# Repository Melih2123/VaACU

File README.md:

# VaACU
**Voltage and Amperage Control Unit**

VaACU is an open-source power management and battery charging platform designed to integrate multiple power sources into a single, organized system.

It supports **9–36 V DC input** and **220 V AC mains input**, converting incoming power into regulated **3.3 V, 5 V, and 12 V DC rails** while supporting battery charging, power-path management, current monitoring, and protection circuitry.

### Key Features
- Multiple power input options
- Regulated 3.3 V, 5 V, and 12 V power rails
- Integrated battery charging and backup power management
- Diode OR-ing for power-source isolation
- Current sensing using the INA293B2
- Fuse-based overcurrent protection
- Battery undervoltage protection
- ESP32-S3-based monitoring and control
- Open-source hardware design developed with KiCad

VaACU aims to provide a modular foundation for embedded systems that need flexible power input, battery backup, and centralized power management.

**Status:** Hardware design and validation hasnt been done, you the user might have to verify before usage.

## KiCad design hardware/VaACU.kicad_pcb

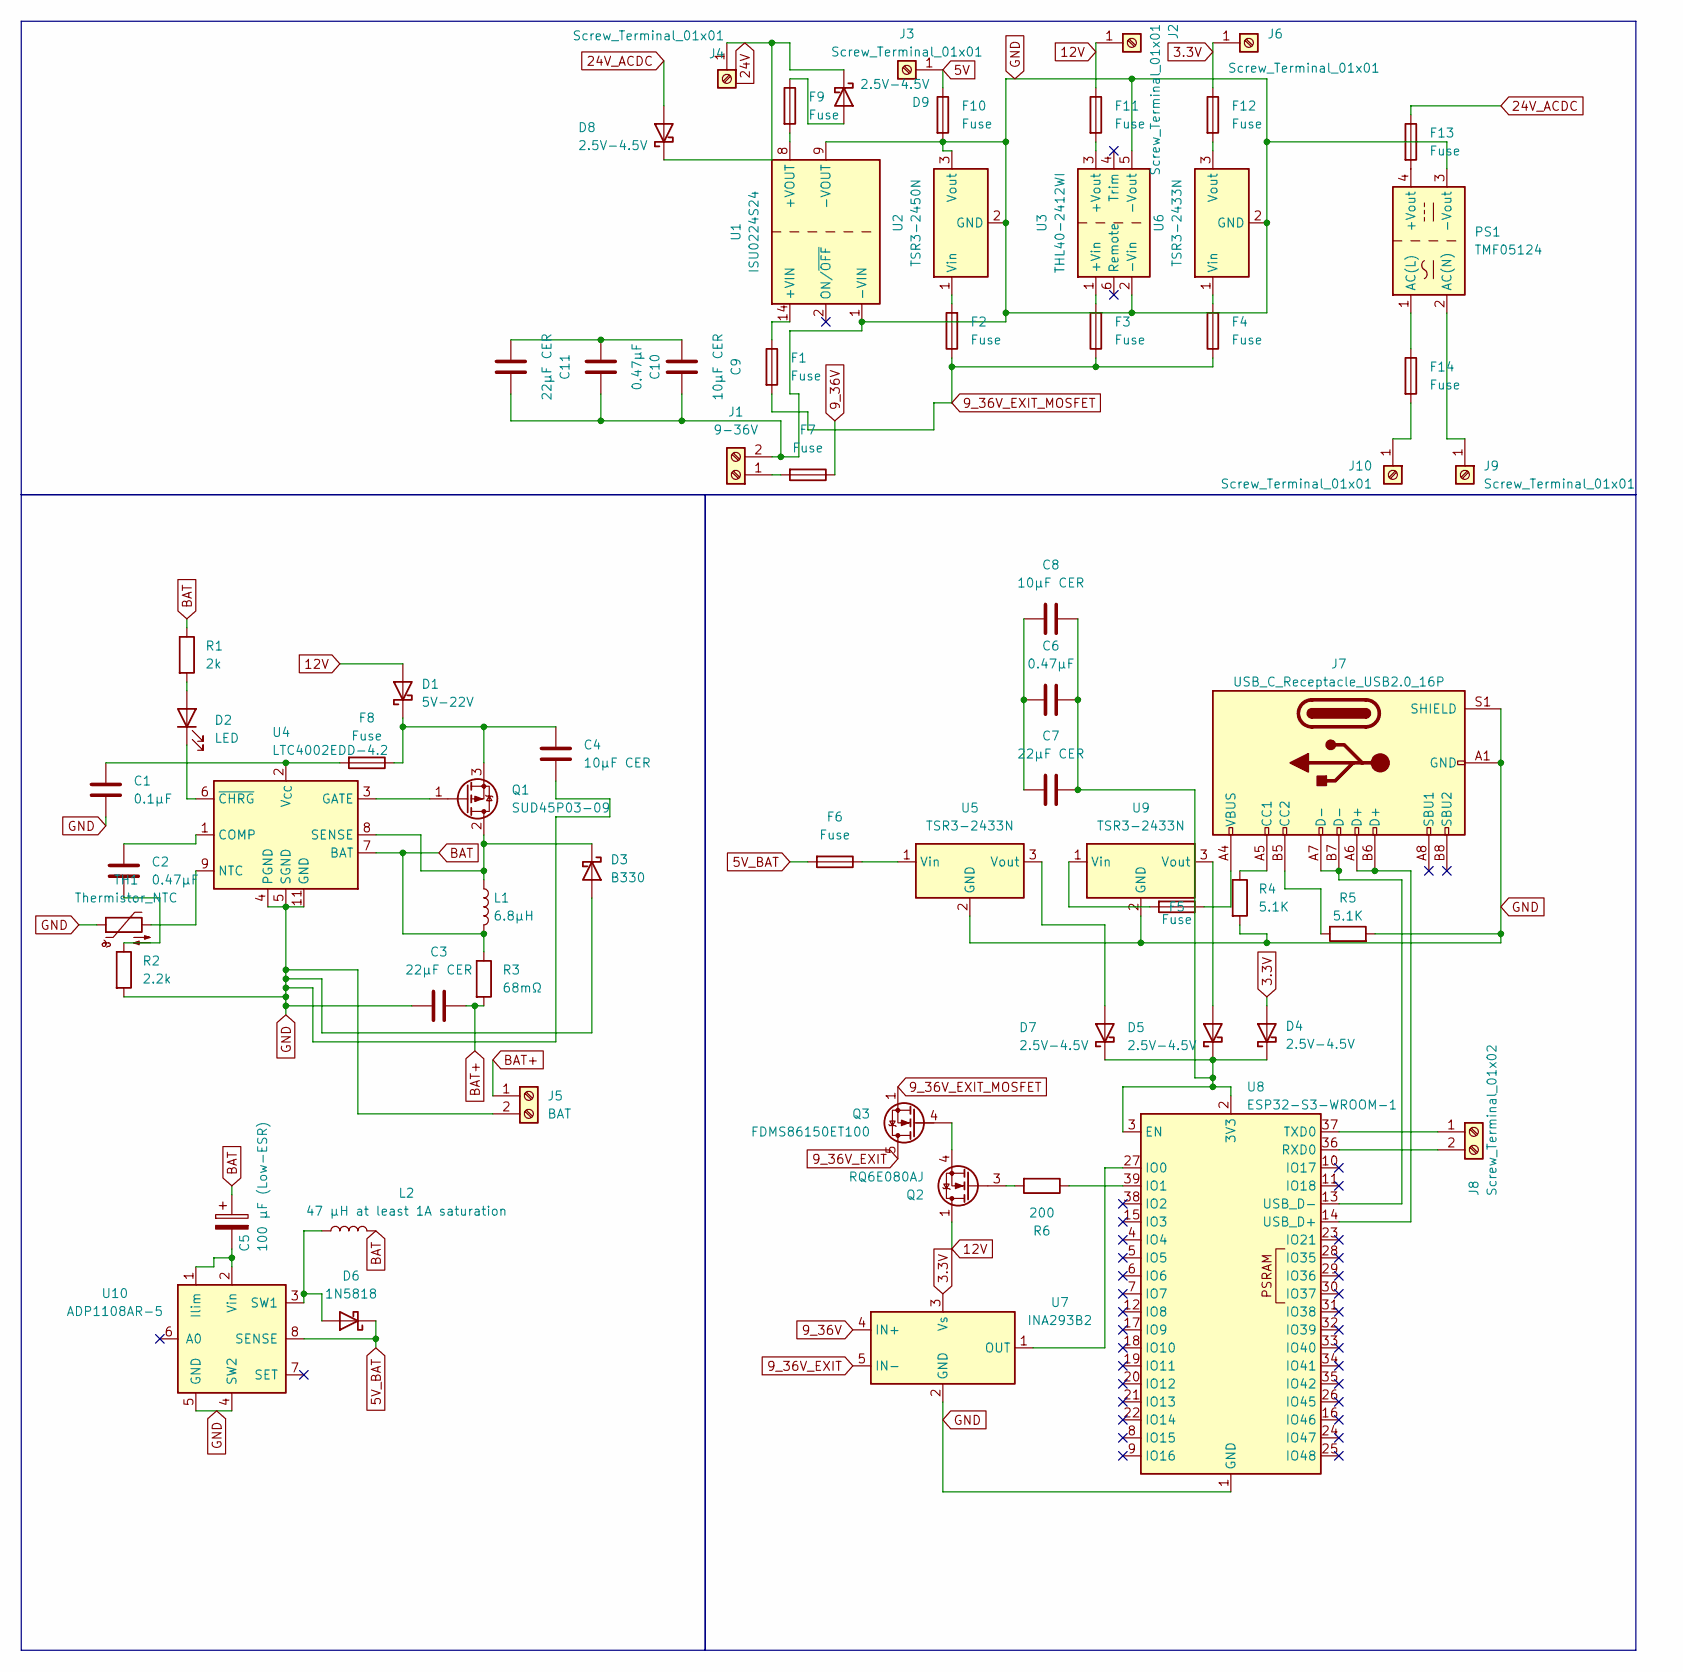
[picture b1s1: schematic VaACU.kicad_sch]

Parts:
C1: 0.1µF; C_0201_0603Metric
C2, C6, C10: 0.47µF; C_0201_0603Metric_Pad0.64x0.40mm_HandSolder
C3, C7, C11: 22µF CER; C_0402_1005Metric
C4, C8, C9: 10µF CER; C_0402_1005Metric
C5: 100 µF (Low-ESR); CP_Elec_3x5.3
D1: 5V-22V; D_1206_3216Metric
D2: LED; LED_0402_1005Metric_Pad0.77x0.64mm_HandSolder
D3: B330; D_SMC
D4, D5, D7, D8, D9: 2.5V-4.5V; D_1206_3216Metric
D6: 1N5818; D_DO-41_SOD81_P10.16mm_Horizontal
F1, F2, F3, F4, F5, F6, F7, F8, F9, F10, F11, F12, F13, F14: Fuse; Fuse_Blade_ATO_directSolder
J1: 9-36V; TerminalBlock_MetzConnect_Type703_RT10N02HGLU_1x02_P9.52mm_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
J2, J3, J4, J6: Screw_Terminal_01x01; TerminalBlock_MetzConnect_360322_1x01_Horizontal_ScrewM3.0_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
J5: BAT; TerminalBlock_MetzConnect_Type703_RT10N02HGLU_1x02_P9.52mm_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
J7: USB_C_Receptacle_USB2.0_16P; USB_C_Receptacle_G-Switch_GT-USB-7010ASV
J8: Screw_Terminal_01x02; TerminalBlock_Xinya_XY308-2.54-2P_1x02_P2.54mm_Horizontal
J9, J10: Screw_Terminal_01x01; Wuerth_REDCUBE-THR_WP-THRSH_74651195_THR
L1: 6.8µH; L_6.3x6.3_H3
L2: 47 µH at least 1A saturation; L_6.3x6.3_H3
PS1: TMF05124; Converter_ACDC_TRACO_TMF_051xx_THT
Q1: SUD45P03-09; TO-252-2
Q2: RQ6E080AJ; TSOT-23-6
Q3: FDMS86150ET100; TDSON-8-1
R1: 2k; R_0201_0603Metric
R2: 2.2k; R_0201_0603Metric
R3: 68mΩ; R_0201_0603Metric
R4, R5: 5.1K; R_0201_0603Metric
R6: 200; R_0201_0603Metric
TH1: Thermistor_NTC; R_0603_1608Metric
U1: ISU0224S24; Converter_DCDC_XP_POWER-ISU02_SMD
U2: TSR3-2450N; Converter_DCDC_TRACO_TSR2-24xxN_TSR2-24xxxN_THT
U3: THL40-2412WI; Converter_DCDC_TRACO_THL40-xxxxWI_THT
U4: LTC4002EDD-4.2; DFN-10-1EP_3x3mm_P0.5mm_EP1.646x3.1mm_ThermalVias
U5, U6, U9: TSR3-2433N; Converter_DCDC_TRACO_TSR2-24xxN_TSR2-24xxxN_THT
U7: INA293B2; SOT-23-5
U8: ESP32-S3-WROOM-1
U10: ADP1108AR-5; SOIC-8_3.9x4.9mm_P1.27mm

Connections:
3.3V: D4.2 (A), F12.1, J6.1, U7.3 (Vs)
5V: F10.1, J3.1
5V_BAT: D6.1 (K), F6.2, U10.8 (SENSE)
9_36V: F7.1, U7.4 (IN+)
9_36V_EXIT: Q3.5 (D), U7.5 (IN-)
9_36V_EXIT_MOSFET: F1.2, F2.1, F3.1, F4.1, Q3.1 (S), Q3.2 (S), Q3.3 (S)
12V: D1.2 (A), F11.1, J2.1, Q2.1 (D), Q2.2 (D), Q2.5 (D), Q2.6 (D)
24V: D8.1 (K), D9.1 (K), J4.1
24V_ACDC: D8.2 (A), F13.1
BAT: C5.1, L1.2, L2.2, R1.1, R3.1, U4.7 (BAT)
BAT+: C3.2, J5.1, R3.2
GND: C1.2, C3.1, C4.1, C9.2, C10.1, C11.1, D3.2 (A), F10.2, J1.2, J5.2, J7.A1 (GND), J7.A12 (GND), J7.B1 (GND), J7.B12 (GND), J7.S1 (SHIELD), PS1.3 (-Vout), R2.2, R4.2, R5.2, TH1.1, U1.1 (-VIN), U1.9 (-VOUT), U2.2 (GND), U2.3 (Vout), U3.2 (-Vin), U3.5 (-Vout), U4.4 (PGND), U4.5 (SGND), U4.11 (GND), U5.2 (GND), U6.2 (GND), U7.2 (GND), U8.1 (GND), U8.40 (GND), U8.41 (GND), U9.2 (GND), U10.4 (SW2), U10.5 (GND)
unnamed: C2.2, R2.1
unnamed: C6.2, C7.2, C8.1
unnamed: C9.1, C10.2, C11.2
unnamed: C4.2, D1.1 (K), F8.1, Q1.3 (S)
unnamed: D2.2 (A), R1.2
unnamed: D2.1 (K), U4.6 (~CHRG)
unnamed: D3.1 (K), L1.1, Q1.2 (D), U4.8 (SENSE)
unnamed: C6.1, C7.1, C8.2, D4.1 (K), D5.1 (K), D7.1 (K), U8.2 (3V3), U8.3 (EN)
unnamed: D5.2 (A), U9.3 (Vout)
unnamed: D6.2 (A), L2.1, U10.3 (SW1)
unnamed: D7.2 (A), U5.3 (Vout)
unnamed: D9.2 (A), F9.1
unnamed: F5.1, J7.A4 (VBUS), J7.A9 (VBUS), J7.B4 (VBUS), J7.B9 (VBUS)
unnamed: F7.2, J1.1
unnamed: J7.A5 (CC1), R4.1
unnamed: J7.B5 (CC2), R5.1
unnamed: J8.1, U8.37 (TXD0)
unnamed: J8.2, U8.36 (RXD0)
unnamed: J9.1, PS1.2 (AC(N))
unnamed: F14.2, J10.1
unnamed: F13.2, PS1.4 (+Vout)
unnamed: F14.1, PS1.1 (AC(L))
unnamed: Q1.1 (G), U4.3 (GATE)
unnamed: Q2.3 (G), R6.2
unnamed: Q2.4 (S), Q3.4 (G)
unnamed: F1.1, U1.14 (+VIN)
unnamed: F9.2, U1.8 (+VOUT)
unnamed: F2.2, U2.1 (Vin)
unnamed: F3.2, U3.1 (+Vin)
unnamed: F11.2, U3.3 (+Vout)
unnamed: C2.1, U4.1 (COMP)
unnamed: TH1.2, U4.9 (NTC)
unnamed: C1.1, F8.2, U4.2 (V_{CC})
unnamed: F6.1, U5.1 (Vin)
unnamed: F4.2, U6.1 (Vin)
unnamed: F12.2, U6.3 (Vout)
unnamed: U7.1 (OUT), U8.27 (IO0)
unnamed: R6.1, U8.39 (IO1)
unnamed: J7.A6 (D+), J7.B6 (D+), U8.14 (USB_D+)
unnamed: J7.A7 (D-), J7.B7 (D-), U8.13 (USB_D-)
unnamed: F5.2, U9.1 (Vin)
unnamed: C5.2, U10.1 (Ilim), U10.2 (Vin)

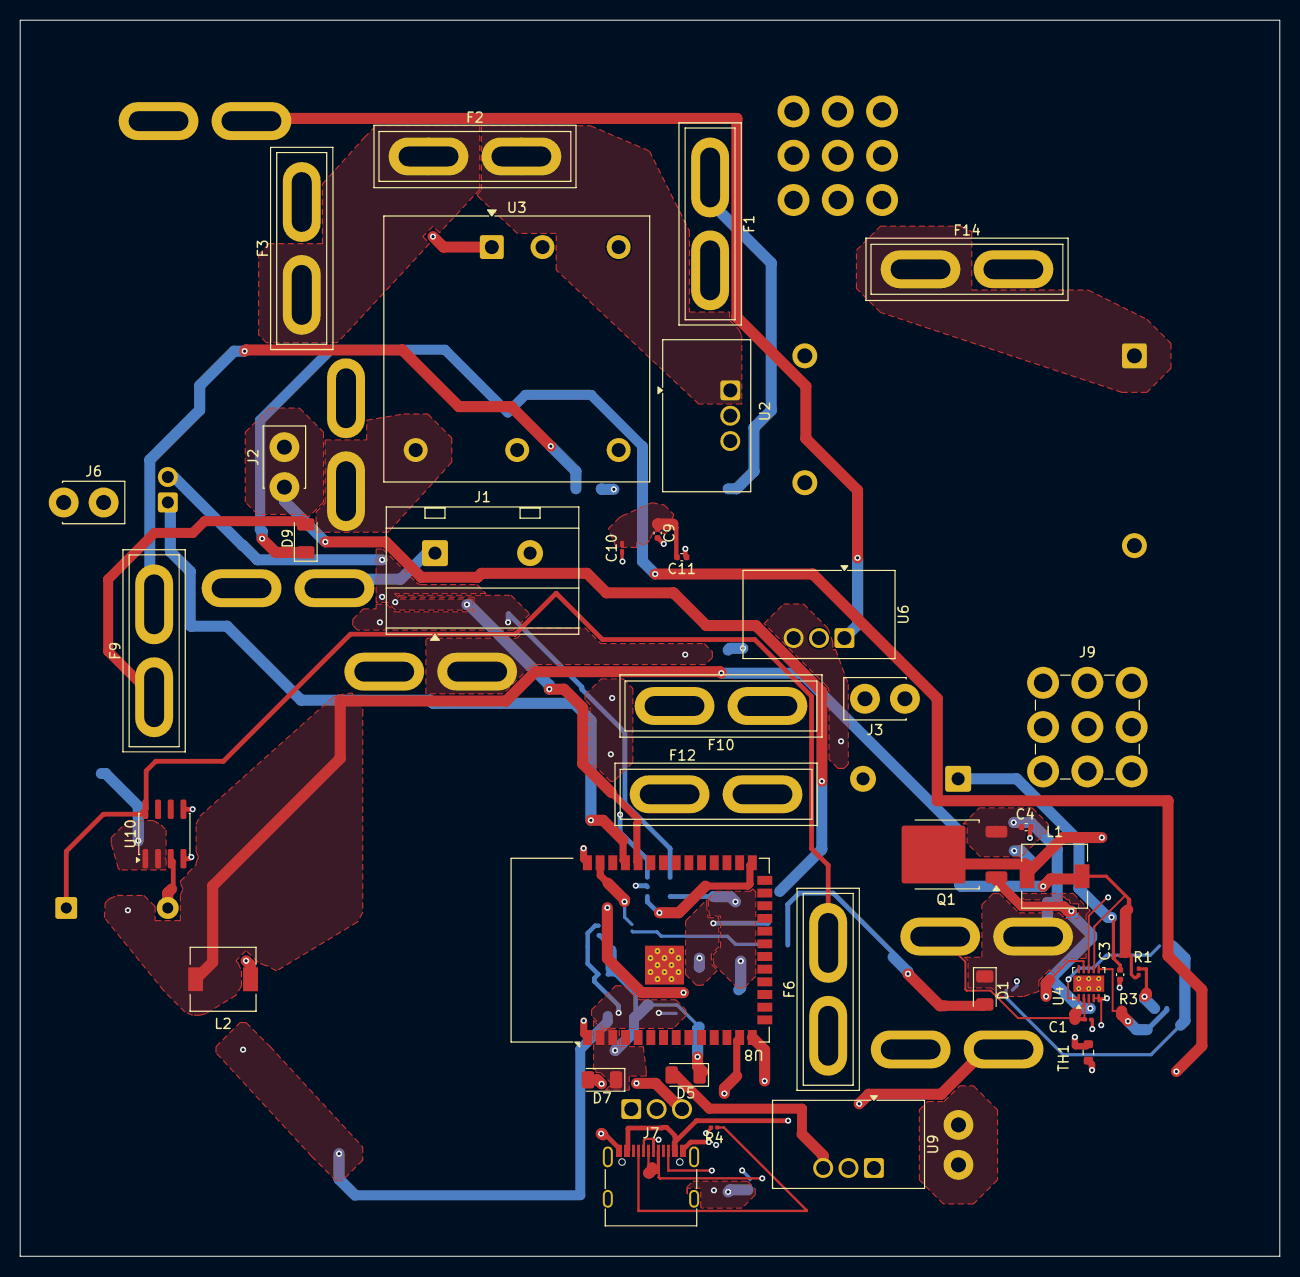
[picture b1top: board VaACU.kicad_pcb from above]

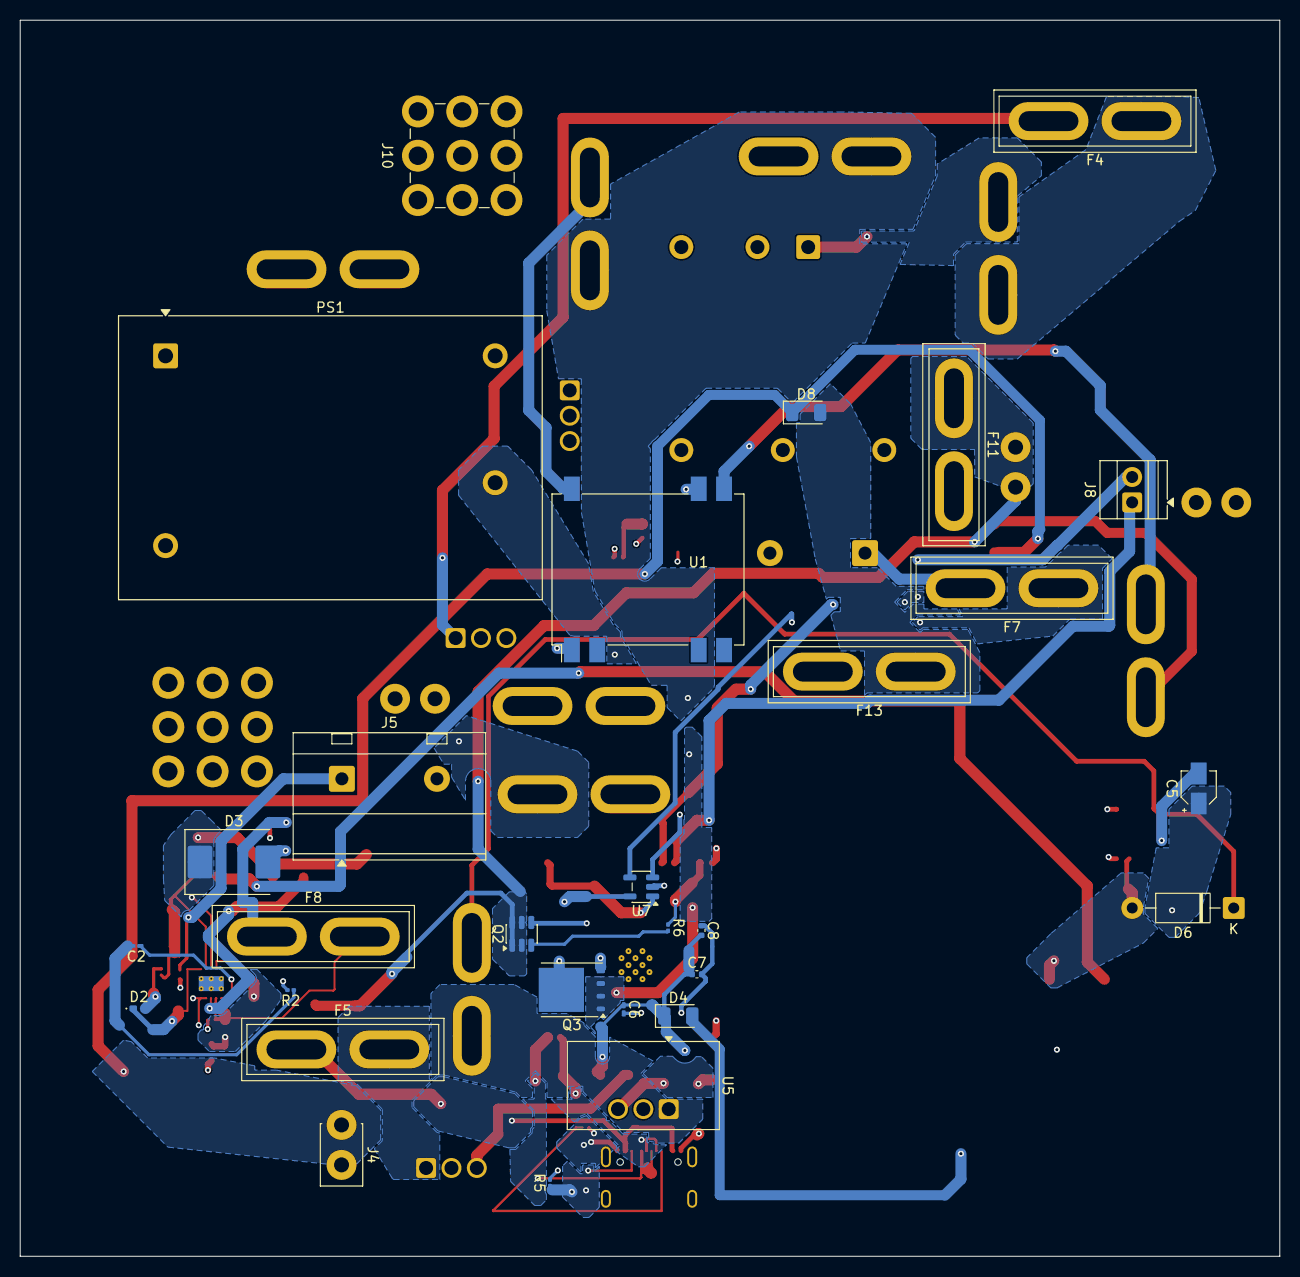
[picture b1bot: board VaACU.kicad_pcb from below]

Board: 4 copper layers, 126.1 x 123.7 mm, 67 parts (29 on the bottom side), 54 nets.
